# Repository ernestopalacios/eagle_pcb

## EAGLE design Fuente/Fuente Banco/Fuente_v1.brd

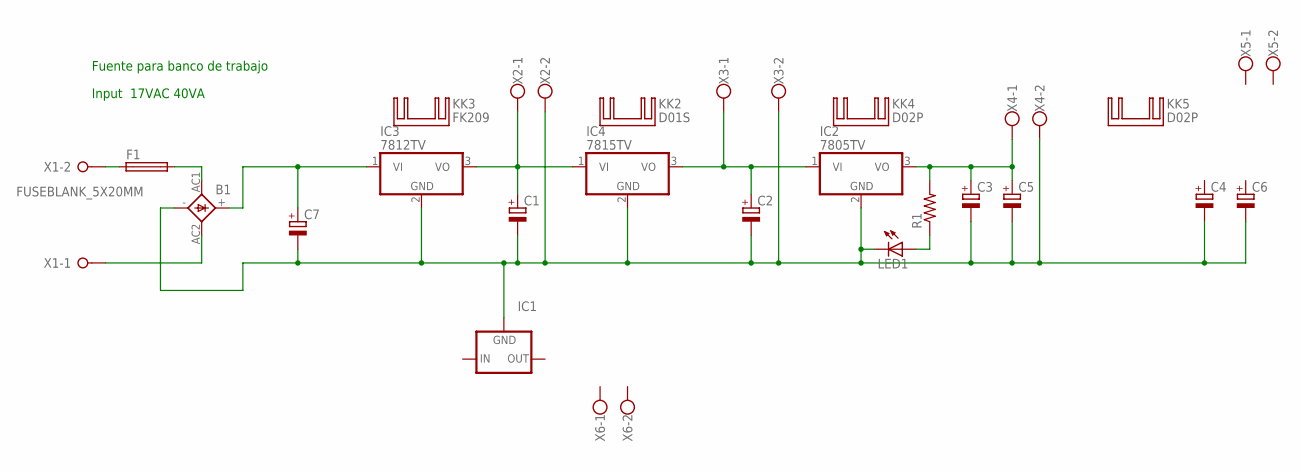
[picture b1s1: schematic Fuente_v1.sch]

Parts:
B1: S51
C1, C2, C3, C7: CPOL-EUE2.5-7; E2,5-7
C4, C5, C6: CPOL-EUE2.5-6; E2,5-6
F1: FUSEBLANK_5X20MM; FUSE_HOLDER_5X20MM
IC1: 79XX-TO3; TO3-79
IC2: 7805TV; TO220V
IC3: 7812TV; TO220V
IC4: 7815TV; TO220V
KK2: D01S
KK3: FK209
KK4, KK5: D02P; D02PA
LED1: LED5MM
R1: R-US_0204/7; 0204/7
X1: W237-02P; W237-132
X2, X3, X4, X5, X6: W237-102

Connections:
unnamed: B1.-, C1.-, C2.-, C3.-, C4.-, C5.-, C6.-, C7.-, IC1.2 (GND), IC2.2 (GND), IC3.2 (GND), IC4.2 (GND), LED1.K (C), X2.2, X3.2, X4.2
unnamed: B1.+, C7.+, IC3.1 (VI)
unnamed: C1.+, IC3.3 (VO), IC4.1 (VI), X2.1
unnamed: C2.+, IC2.1 (VI), IC4.3 (VO), X3.1
unnamed: C3.+, C5.+, IC2.3 (VO), R1.2, X4.1
unnamed: LED1.A, R1.1
unnamed: B1.AC1, F1.2
unnamed: B1.AC2, X1.1
unnamed: F1.1, X1.2

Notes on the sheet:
Fuente para banco de trabajo
Input 17VAC 40VA

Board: 2 copper layers, 25 parts (0 on the bottom side), 9 nets, no tracks yet.

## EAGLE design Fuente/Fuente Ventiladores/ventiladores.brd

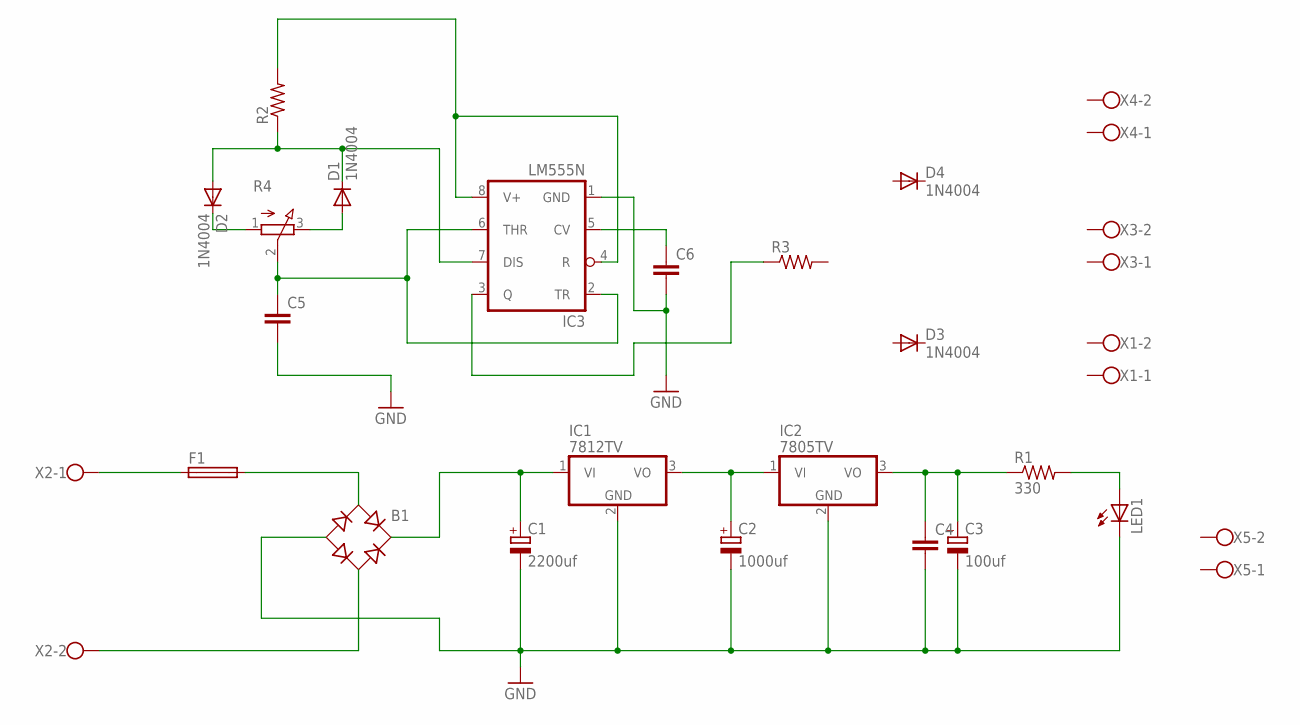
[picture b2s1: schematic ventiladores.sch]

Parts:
B1: RB1A
C1: 2200uf; E5-13
C2: 1000uf; E5-10,5
C3: 100uf; E2,5-6
C4, C5, C6: C2.5/2; C2.5-2
D1, D2, D3, D4: 1N4004; DO41-10
F1: GSH15
IC1: 7812TV; TO220V
IC2: 7805TV; TO220V
IC3: LM555N; DIL08
LED1: LED5MM
R1: 330; 0204/5
R2, R3: R-US_0207/7; 0207/7
R4: 3RP/1610N
X1, X3, X4, X5: W237-102; MPN 237-102
X2: W237-102

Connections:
GND: B1.-, C1.-, C2.-, C3.-, C4.2, C5.2, C6.2, IC1.2 (GND), IC2.2 (GND), IC3.1 (GND), LED1.K (C)
unnamed: F1.1, X2.1
unnamed: B1.AC1, F1.2
unnamed: B1.AC2, X2.2
unnamed: B1.+, C1.+, IC1.1 (VI)
unnamed: C2.+, IC1.3 (VO), IC2.1 (VI)
unnamed: C3.+, C4.1, IC2.3 (VO), R1.1
unnamed: LED1.A, R1.2
unnamed: D2.C, R4.1 (A)
unnamed: D1.A, R4.3 (E)
unnamed: D1.C, D2.A, IC3.7 (DIS), R2.1
unnamed: C5.1, IC3.2 (TR), IC3.6 (THR), R4.2 (S)
unnamed: IC3.3 (Q), R3.1
unnamed: IC3.4 (R), IC3.8 (V+), R2.2
unnamed: C6.1, IC3.5 (CV)

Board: 2 copper layers, 25 parts (0 on the bottom side), 15 nets, no tracks yet.

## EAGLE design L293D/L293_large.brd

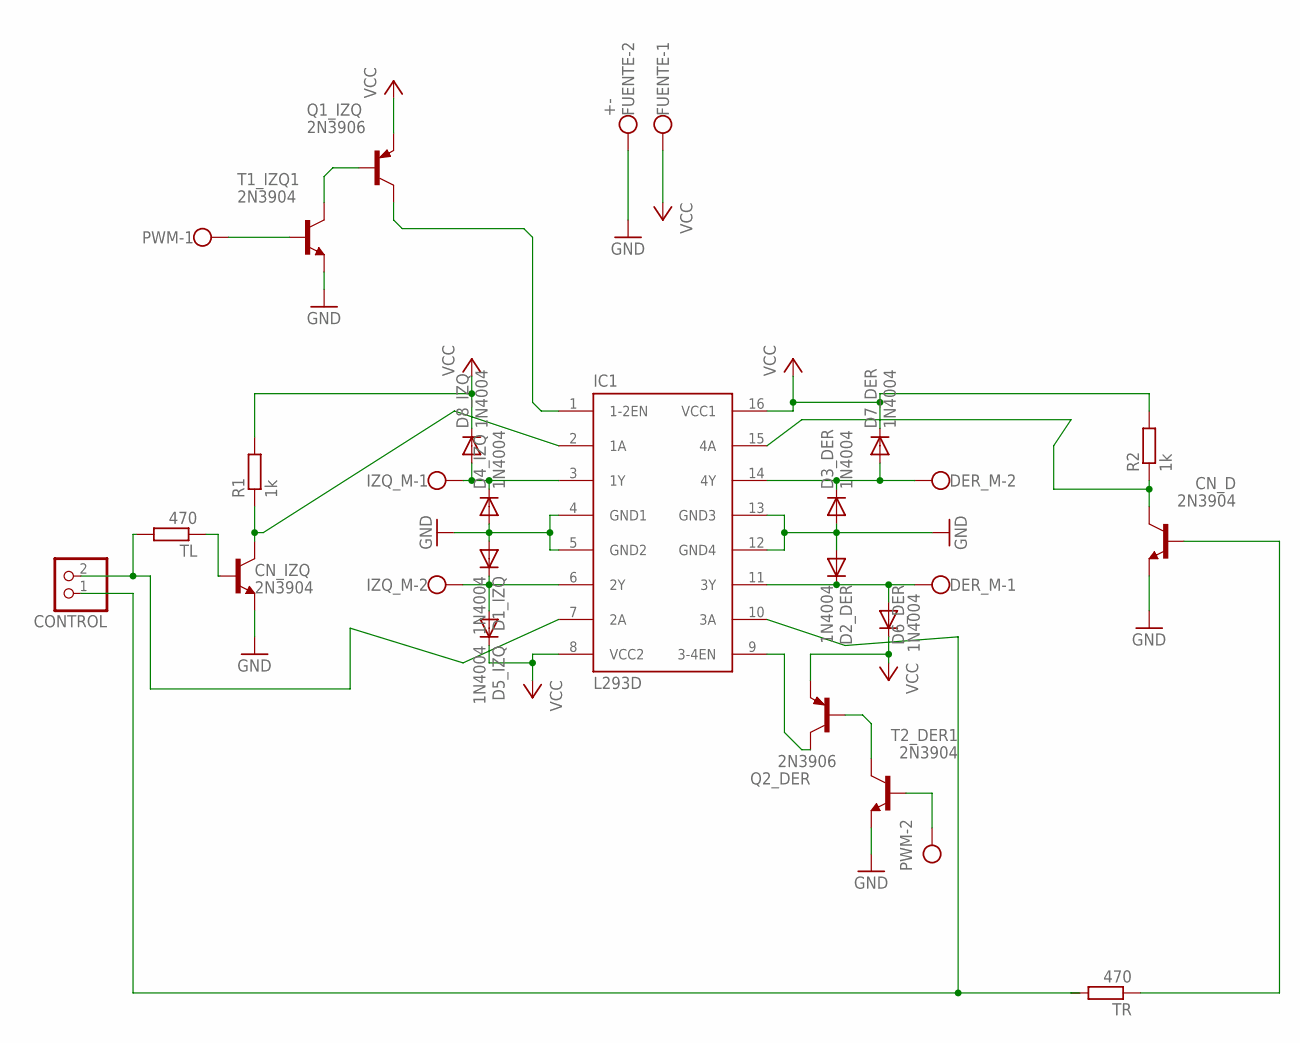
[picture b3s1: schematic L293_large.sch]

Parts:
CN_D: 2N3904; TO92
CN_IZQ: 2N3904; TO92
CONTROL: PINHD-1X2/90; 1X02/90
D1_IZQ, D2_DER, D3_DER, D4_IZQ, D5_IZQ, D6_DER, D7_DER, D8_IZQ: 1N4004; DO41-10
DER_M: W237-02P; W237-132
FUENTE: +-; W237-132
IC1: L293D; DIL16
IZQ_M: W237-02P; W237-132
PWM: W237-02P; W237-132
Q1_IZQ, Q2_DER: 2N3906; TO92
R1, R2: 1k; 0207/5V
T1_IZQ1, T2_DER1: 2N3904; TO92
TL: 470; 0207/5V
TR: 470; 0207/5V

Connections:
GND: CN_D.3 (E), CN_IZQ.3 (E), D1_IZQ.A, D2_DER.A, D3_DER.A, D4_IZQ.A, FUENTE.2, IC1.4 (GND1), IC1.5 (GND2), IC1.12 (GND4), IC1.13 (GND3), T1_IZQ1.3 (E), T2_DER1.3 (E)
unnamed: D2_DER.C, D6_DER.A, DER_M.1, IC1.11 (3Y)
unnamed: D3_DER.C, D7_DER.A, DER_M.2, IC1.14 (4Y)
unnamed: D1_IZQ.C, D5_IZQ.A, IC1.6 (2Y), IZQ_M.2
unnamed: D4_IZQ.C, D8_IZQ.A, IC1.3 (1Y), IZQ_M.1
unnamed: CONTROL.2, IC1.7 (2A), TL.2
unnamed: CN_IZQ.2 (B), TL.1
unnamed: CN_IZQ.1 (C), IC1.2 (1A), R1.1
unnamed: CN_D.2 (B), TR.1
unnamed: CN_D.1 (C), IC1.15 (4A), R2.1
unnamed: Q1_IZQ.2 (B), T1_IZQ1.1 (C)
unnamed: IC1.1 (1-2EN), Q1_IZQ.1 (C)
unnamed: CONTROL.1, IC1.10 (3A), TR.2
unnamed: PWM.1, T1_IZQ1.2 (B)
unnamed: Q2_DER.2 (B), T2_DER1.1 (C)
unnamed: PWM.2, T2_DER1.2 (B)
unnamed: IC1.9 (3-4EN), Q2_DER.1 (C)
VCC: D5_IZQ.C, D6_DER.C, D7_DER.C, D8_IZQ.C, FUENTE.1, IC1.8 (VCC2), IC1.16 (VCC1), Q1_IZQ.3 (E), Q2_DER.3 (E), R1.2, R2.2

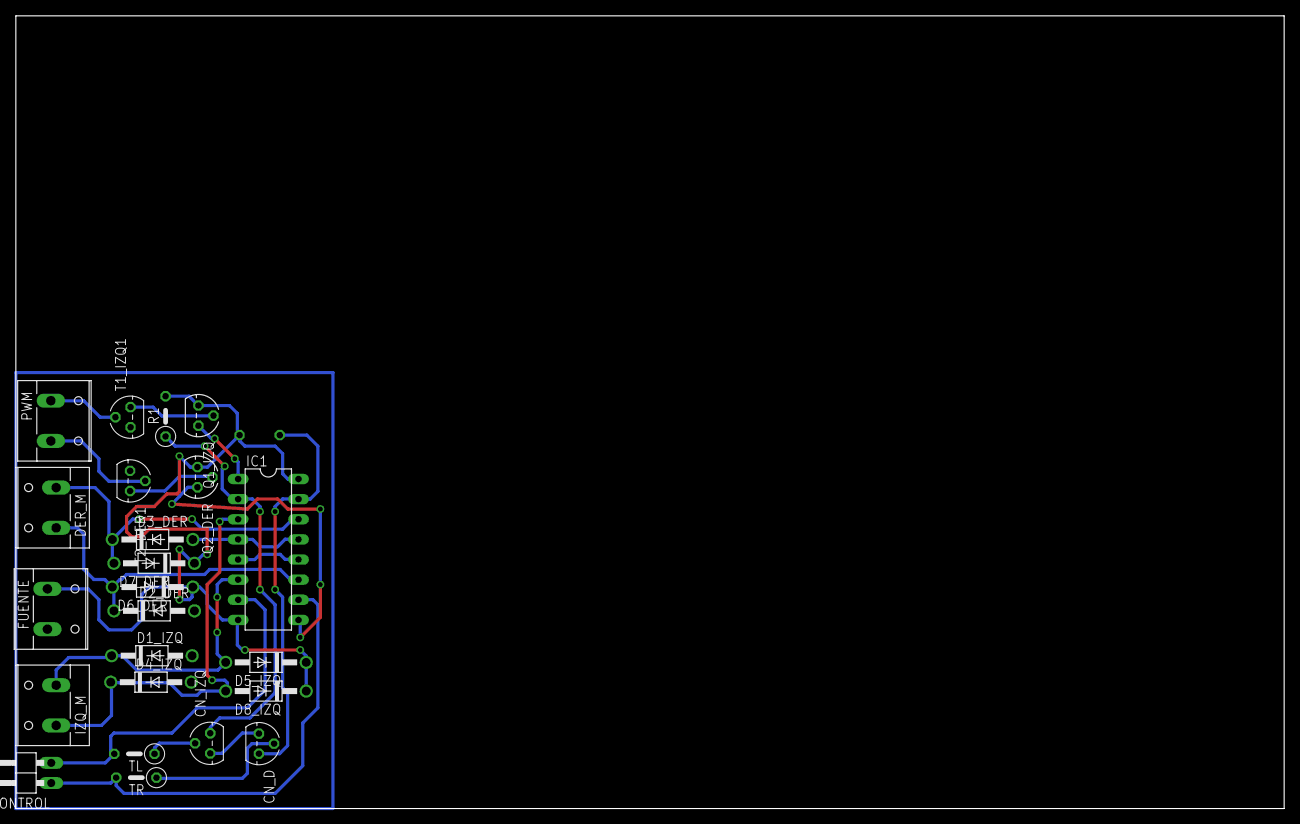
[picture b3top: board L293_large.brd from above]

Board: 2 copper layers, 160.0 x 100.0 mm, 24 parts (1 on the bottom side), 18 nets.
